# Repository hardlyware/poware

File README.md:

# PoWARE⚡

PoWARE is a handy breadboard power supply for the modern maker & engineer. 
 - 🔌 USB-C PD powered
 - ⚙️ Adjustable rail voltages: 3V3–5V
 - 🪛 Screw terminal for direct PD access: 5–20V

## How do I get one?
PoWARE will be available on Tindie when finished. If you're interested, please let me know by e-mail or contacting me on any of my socials.

## Licenses
PoWARE hardware is licensed under CERN-OHL-S-2.0. See LICENSE file.

## 📬 Get in Touch

- 📧 **Email**: [info@hardlyware.com](mailto:info@hardlyware.com)
- 📸 **Instagram**: [@hardlyware](https://www.instagram.com/hardlyware/)
- 🎥 **YouTube**: [HARDlyWARE](hhttps://www.youtube.com/@HARDlyWARE)

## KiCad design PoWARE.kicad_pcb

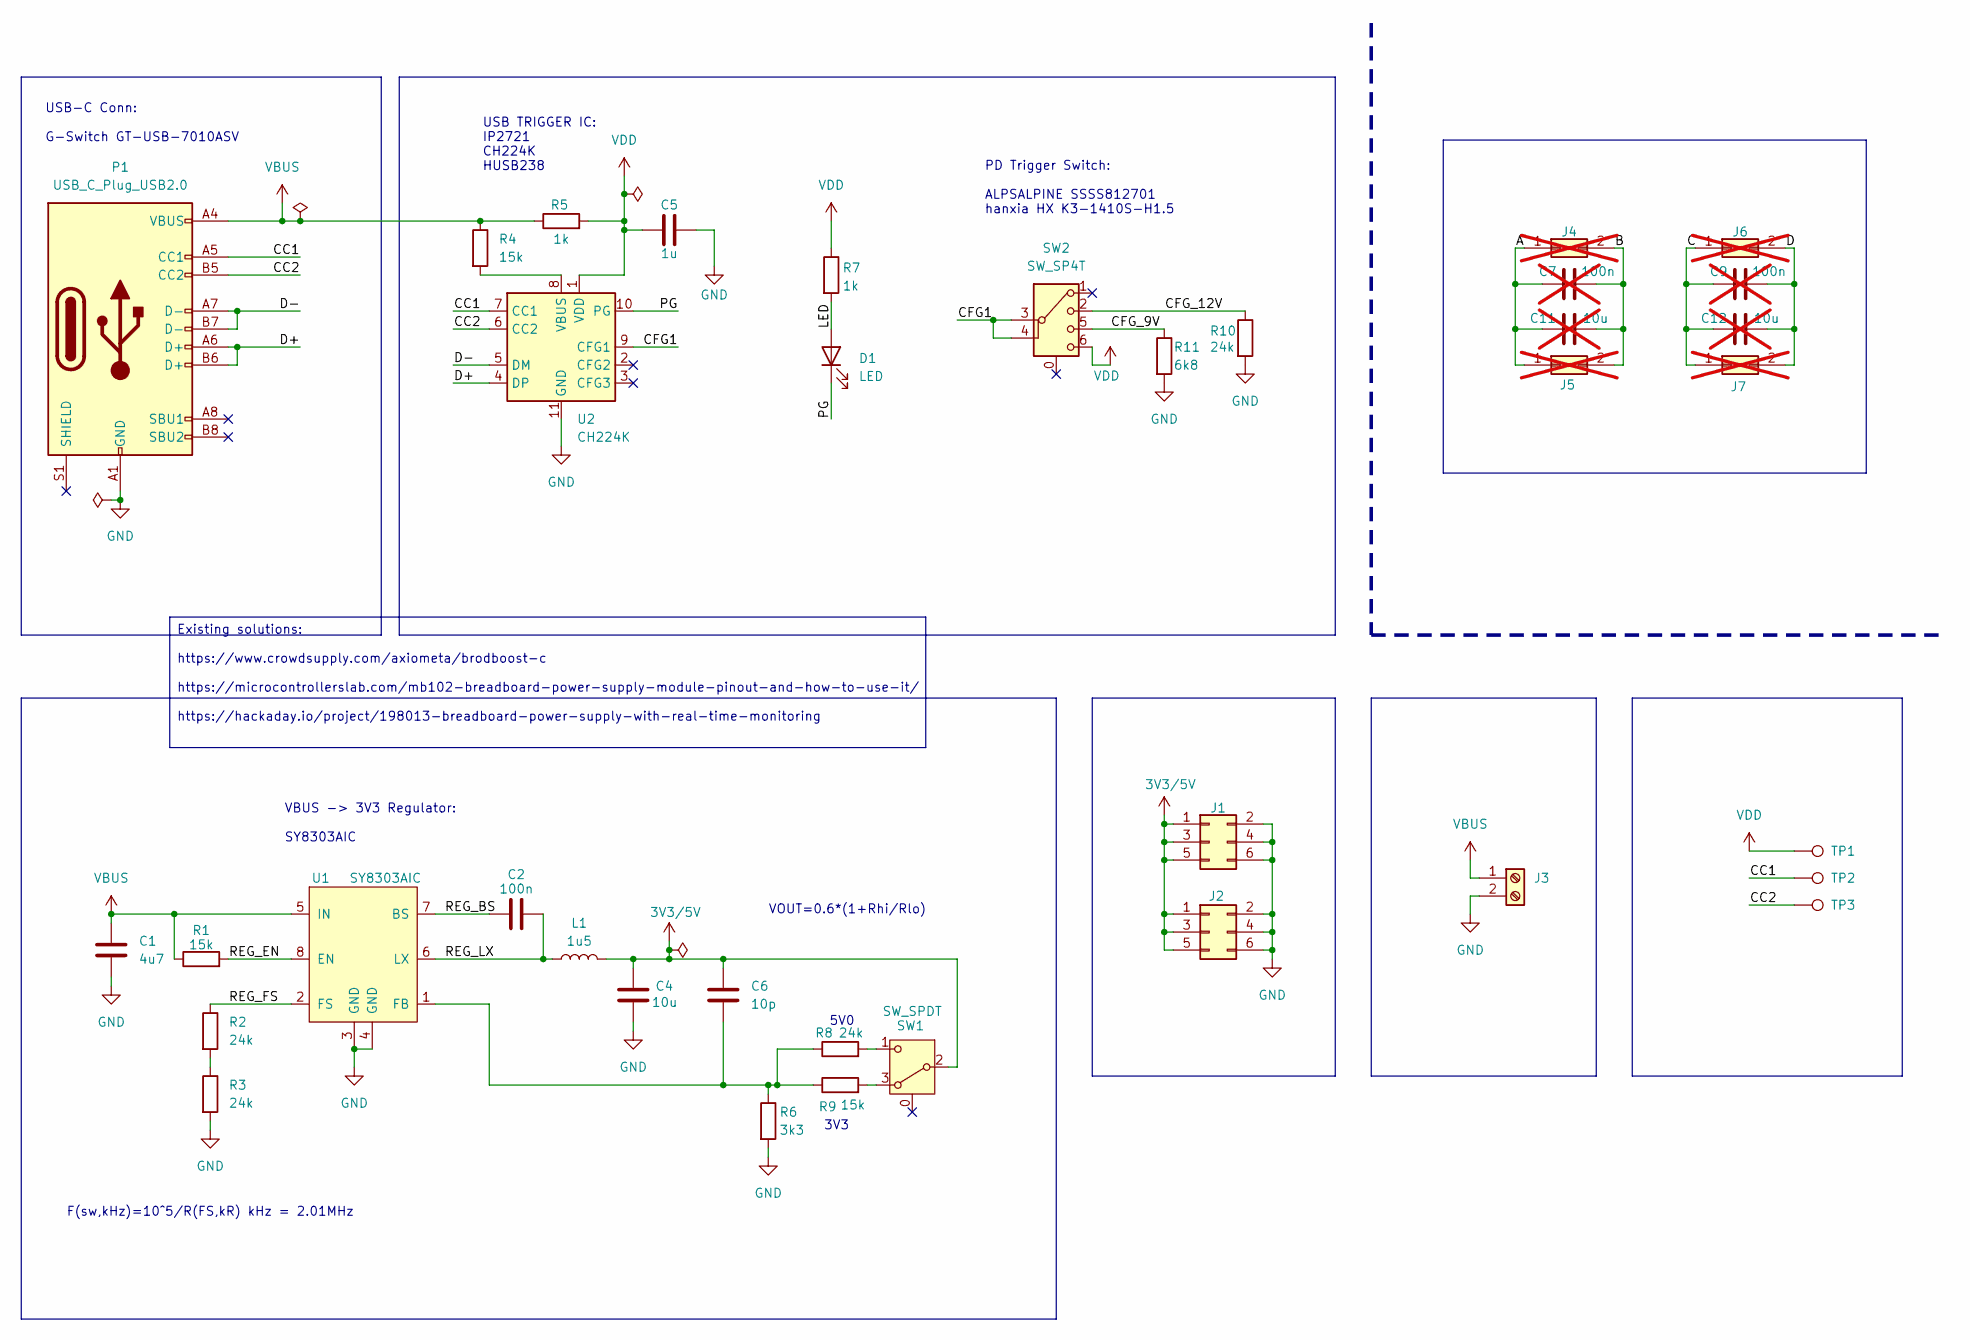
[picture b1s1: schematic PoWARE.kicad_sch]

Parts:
C1: 4u7; C_0805_2012Metric
C2: 100n; C_0603_1608Metric
C4: 10u; C_0805_2012Metric
C5: 1u; C_0603_1608Metric
C6: 10p; C_0603_1608Metric
C7, C9: 100n; C_0603_1608Metric; not fitted
C11, C12: 10u; C_0805_2012Metric; not fitted
D1: LED; LED_0603_1608Metric
J1, J2: Conn_02x03_Counter_Clockwise; PinHeader_2x03_P2.54mm_Vertical
J3: Screw_Terminal_01x02; DB301V-3.5-2P-GN-S
J4, J5, J6, J7: Conn_02x01; PinHeader_2x01_P2.54mm_Vertical; not fitted
L1: 1u5; FXL0420-1R5-M
P1: USB_C_Plug_USB2.0; USB_C_Receptacle_HCTL_HC-TYPE-C-16P-01A
R1, R4, R9: 15k; R_0603_1608Metric
R2, R3, R8, R10: 24k; R_0603_1608Metric
R5, R7: 1k; R_0603_1608Metric
R6: 3k3; R_0603_1608Metric
R11: 6k8; R_0603_1608Metric
SW1: SW_SPDT; SSSS811101
SW2: SW_SP4T; SSSS812701
TP1, TP2, TP3: TestPoint; TestPoint_Pad_D1.0mm
U1: SY8303AIC
U2: CH224K; CH224K-SSOP-10-1EP

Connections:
3V3/5V: C4.1, C6.2, J1.1, J1.3, J1.5, J2.1, J2.3, J2.5, L1.2, SW1.2 (B)
/A: C7.1, C11.1, J4.1, J5.1
/B: C7.2, C11.2, J4.2, J5.2
/C: C9.1, C12.1, J6.1, J7.1
/CC1: P1.A5 (CC1), TP2.1, U2.7 (CC1)
/CC2: P1.B5 (CC2), TP3.1, U2.6 (CC2)
/CFG1: SW2.3, SW2.4, U2.9 (CFG1)
/CFG_9V: R11.1, SW2.5
/CFG_12V: R10.1, SW2.2
/D: C9.2, C12.2, J6.2, J7.2
/D+: P1.A6 (D+), P1.B6 (D+), U2.4 (DP)
/D-: P1.A7 (D-), P1.B7 (D-), U2.5 (DM)
/LED: D1.2 (A), R7.2
/PG: D1.1 (K), U2.10 (PG)
/REG_BS: C2.1, U1.7 (BS)
/REG_EN: R1.2, U1.8 (EN)
/REG_FS: R2.1, U1.2 (FS)
/REG_LX: C2.2, L1.1, U1.6 (LX)
GND: C1.2, C4.2, C5.2, J1.2, J1.4, J1.6, J2.2, J2.4, J2.6, J3.2, P1.A1 (GND), P1.A12 (GND), P1.B1 (GND), P1.B12 (GND), R3.2, R6.2, R10.2, R11.2, U1.3 (GND), U1.4 (GND), U2.11 (GND)
unnamed: R2.2, R3.1
unnamed: R8.2, SW1.1 (A)
unnamed: R9.2, SW1.3 (C)
unnamed: C6.1, R6.1, R8.1, R9.1, U1.1 (FB)
unnamed: R4.2, U2.8 (VBUS)
VBUS: C1.1, J3.1, P1.A4 (VBUS), P1.A9 (VBUS), P1.B4 (VBUS), P1.B9 (VBUS), R1.1, R4.1, R5.1, U1.5 (IN)
VDD: C5.1, R5.2, R7.1, SW2.6, TP1.1, U2.1 (VDD)

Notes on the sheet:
F(sw,kHz)=10^5/R(FS,kR) kHz = 2.01MHz
3V3
5V0
VBUS -> 3V3 Regulator: SY8303AIC
USB TRIGGER IC: IP2721 CH224K HUSB238
VOUT=0.6*(1+Rhi/Rlo)
USB-C Conn: G-Switch GT-USB-7010ASV
PD Trigger Switch: ALPSALPINE SSSS812701 hanxia HX K3-1410S-H1.5
Existing solutions: https://www.crowdsupply.com/axiometa/brodboost-c https://microcontrollerslab.com/mb102-breadboard-power-supply-module-pinout-and-how-to-use-it/ https://hackaday.io/project/198013-breadboard-power-supply-with-real-time-monitoring

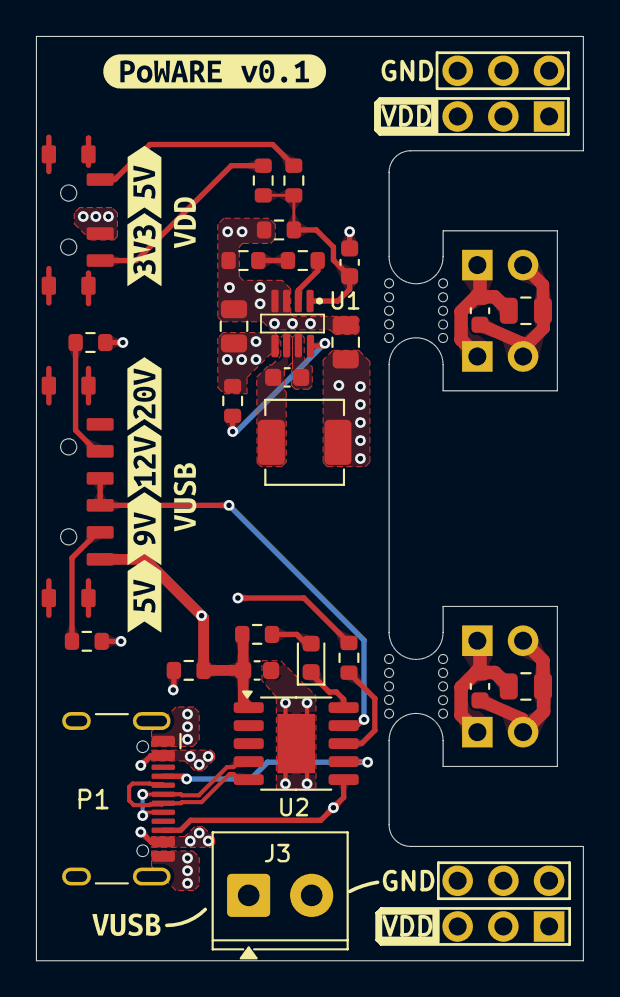
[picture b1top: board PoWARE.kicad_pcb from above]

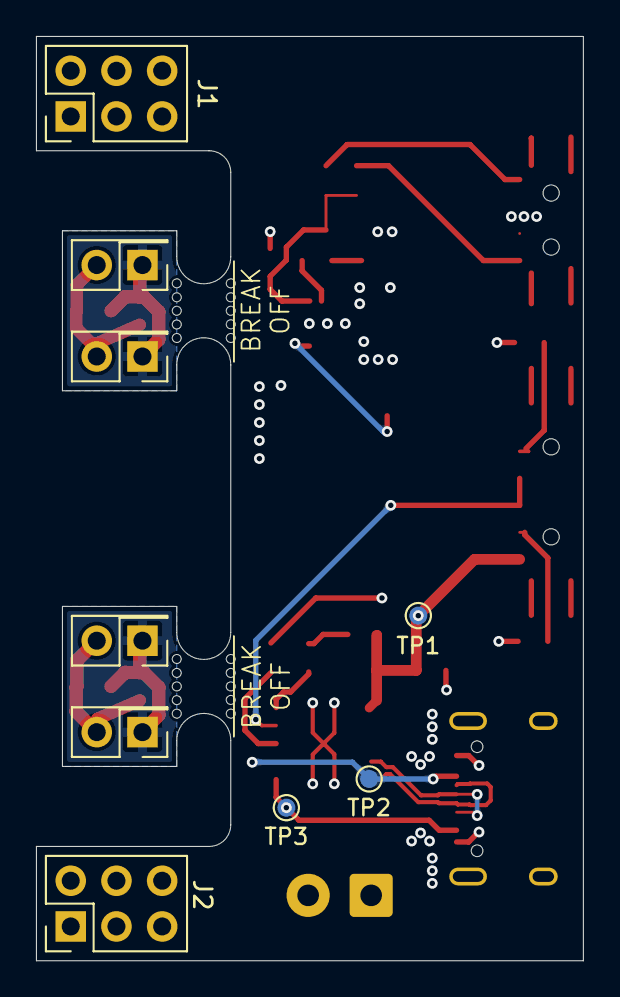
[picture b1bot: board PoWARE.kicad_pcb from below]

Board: 4 copper layers, 30.4 x 51.3 mm, 49 parts (9 on the bottom side), 26 nets.

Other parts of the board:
kibuzzard-68873AFF: G***; kibuzzard-68873AFF
kibuzzard-68873B0E: G***; kibuzzard-68873B0E
kibuzzard-68873B1A: G***; kibuzzard-68873B1A
kibuzzard-68873B2C: G***; kibuzzard-68873B2C
kibuzzard-68873B06: G***; kibuzzard-68873B06
kibuzzard-68873B23: G***; kibuzzard-68873B23
kibuzzard-68873D2B: G***; kibuzzard-68873D2B
kibuzzard-68873D34, kibuzzard-68873D34#2: G***; kibuzzard-68873D34
kibuzzard-6887416B: G***; kibuzzard-6887416B
mouse-bite-3mm-slot, mouse-bite-3mm-slot#2: VAL**; mouse-bite-3mm-slot

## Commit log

2025-07-30 Initial commit v0.1
2025-08-04 Small change to jumperless kicad design files
2025-08-04 Cleaned up repo
